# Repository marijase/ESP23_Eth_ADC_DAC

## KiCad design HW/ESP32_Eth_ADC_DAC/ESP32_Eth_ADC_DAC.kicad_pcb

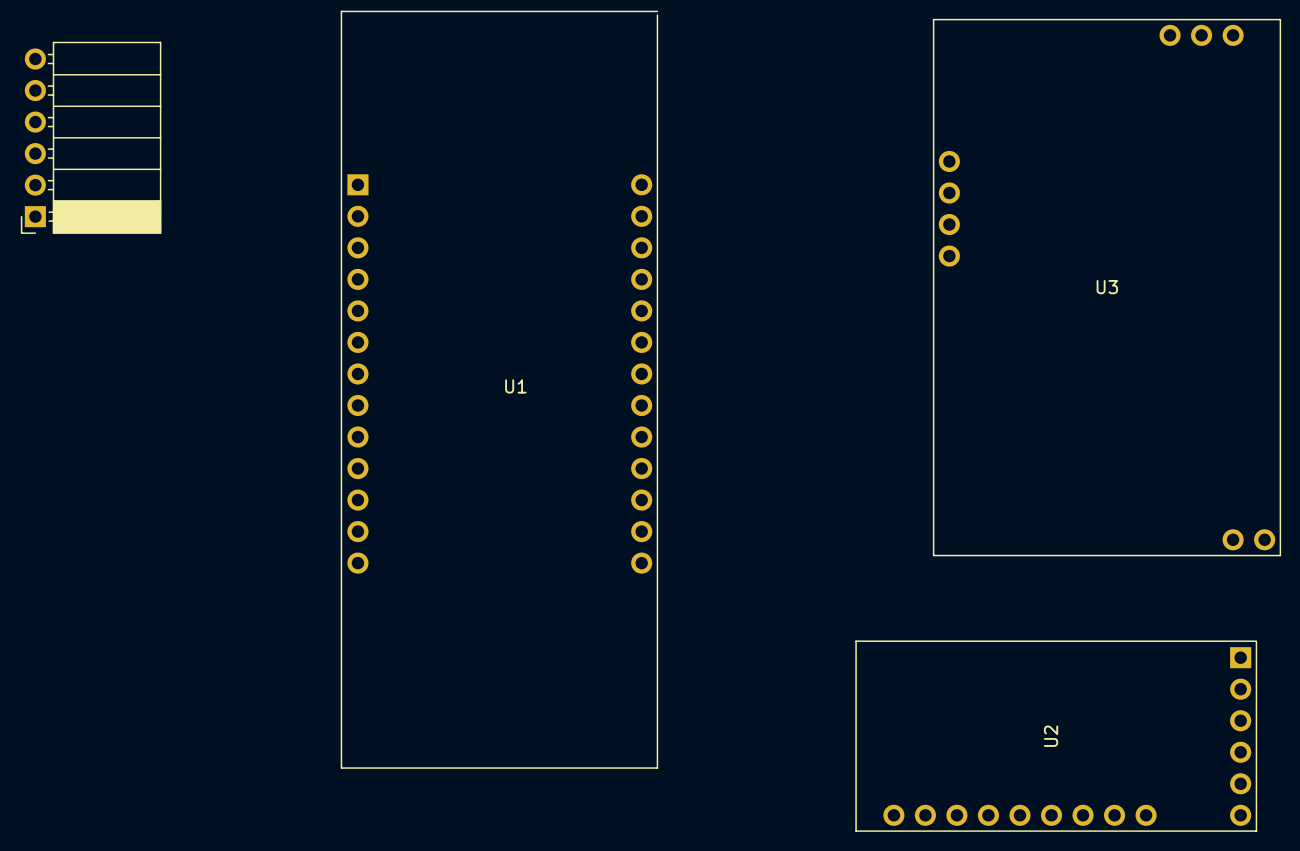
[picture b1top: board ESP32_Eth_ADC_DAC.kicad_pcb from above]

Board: 2 copper layers, 4 parts (0 on the bottom side), 10 nets, no tracks yet.

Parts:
J1: 2.54mm female 90deg; PinSocket_1x06_P2.54mm_Horizontal
U1: ESP32-ETH01
U2: PCM5102A_dac
U3: WM8782S_adc

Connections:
+3.3V: J1.3, U2.11 (A3V3), U2.13 (XSMT)
/DONGLE_2_ESP: J1.4, U1.25 (RXD)
/ESP_2_DONGLE: J1.5, U1.26 (TXD)
/I2S_DATA_IN: U1.17 (IO35), U3.3 (D)
/I2S_DATA_OUT: U1.16 (IO4), U2.3 (DIN)
/I2S_RX_BCLK: U1.21 (IO36), U3.1 (B)
/I2S_RX_LRCLK: U1.22 (IO39), U3.2 (LR)
/I2S_TX_BCLK: U1.20 (IO15), U2.2 (BCK)
/I2S_TX_LRCLK: U1.19 (IO14), U2.4 (LCK)
GND: J1.6, U1.6 (485_EN), U2.1 (SCK), U2.8 (AGND), U2.10 (AGND), U2.12 (FMT), U2.14 (DEMP), U2.15 (FLT)

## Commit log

2026-06-09 KiCad Schematic v1.0
2026-06-26 Version 3.0
2026-06-26 Git fixed
2026-06-26 Version 3.1
2026-06-26 Version 3.2
2026-06-27 added README
